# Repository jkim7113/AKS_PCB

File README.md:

# AKS_PCB
PCB Signal/Powertrain for the UIUC iRobotics Autonomous Kart

Surface Mounted Devices:
- F1 = Littelfuse 0451 (to protect the circuit from overcurrent)
- D1 = SMBJ15A TVS diode (12-input transient suppression)
- U1 = SN65HVD230 (CANBUS Transceiver)
- U2 = Polulu D24V10F5 (12 to 5V converter)

**Use 2oz Cu for /+12V, /+12V_SAFE and /+5V**

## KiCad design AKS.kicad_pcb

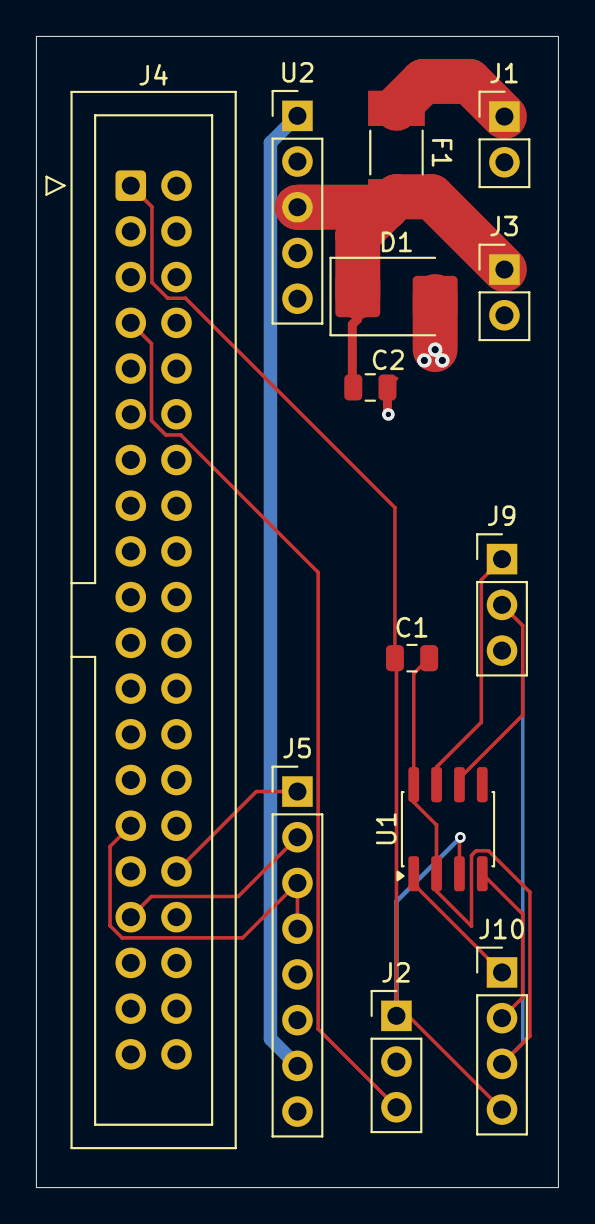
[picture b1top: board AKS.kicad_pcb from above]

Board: 2 copper layers, 29.0 x 63.9 mm, 13 parts (0 on the bottom side), 13 nets.

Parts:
C1, C2: 100nF; C_0805_2012Metric
D1: SMBJ15A TVS diode (12 input transient suppresion); D_SMB
F1: Littelfuse 0451; Fuse_Littelfuse-NANO2-451_453
J1: Power; PinHeader_1x02_P2.54mm_Vertical
J2: Relay board; PinHeader_1x03_P2.54mm_Vertical
J3: JETSON DC JACK; PinHeader_1x02_P2.54mm_Vertical
J4: Jetson 40-pin GPIO; IDC-Header_2x20_P2.54mm_Vertical
J5: BTS7960 H-bridge (signals only); PinHeader_1x08_P2.54mm_Vertical
J9: VESC_CAN; PinHeader_1x03_P2.54mm_Vertical
J10: JETSON_CAN; PinHeader_1x04_P2.54mm_Vertical
U1: SN65HVD230; SOIC-8_3.9x4.9mm_P1.27mm
U2: Polulu D24V10F5 (12 to 5V converter); PinHeader_1x05_P2.54mm_Vertical

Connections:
/+3V3: C1.1, J2.1 (VCC), J4.1 (P1_3V3), J10.4, U1.3 (VCC)
/+5V: J5.7 (VCC), U2.1 (VOUT)
/+12V: F1.1, J1.1 (VCC)
/+12V_SAFE: C2.1, D1.1 (A1), F1.2, J3.1 (VCC), U2.3 (VIN)
/BRAKE_EN: J4.29 (P29_GPIO_EN), J5.3 (R_EN), J5.4 (L_EN)
/BRAKE_LPWM: J4.33 (P33_PWM_LPWM), J5.2 (LPWM)
/BRAKE_RPWM: J4.32 (P32_PWM_RPWM), J5.1 (RPWM)
/CAN_H: J9.1, U1.7 (CANH)
/CAN_L: J9.2, U1.6 (CANL)
/CAN_RX: J10.2, U1.4 (R)
/CAN_TX: J10.1, U1.1 (D)
/GND: C1.2, C2.2, D1.2 (A2), J1.2 (GND), J2.2 (GND), J3.2 (GND), J4.6 (P6_GND), J4.9 (P9_GND), J4.14 (P14_GND), J4.20 (P20_GND), J4.25 (P25_GND), J4.30 (P30_GND), J4.34 (P34_GND), J4.39 (P39_GND), J5.8 (GND), J9.3, J10.3, U1.2 (GND), U1.8 (Rs), U2.2 (GND)
/RELAY_IN: J2.3 (IN), J4.7 (P7_GPIO_RELAY)
